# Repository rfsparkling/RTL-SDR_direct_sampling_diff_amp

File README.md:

This is a breakout board for stock RTL-SDR dongle, allowing the until known best direct sampling method for HF reception using a differential amplifer as BALUN. Right now filtering DC...14 MHz band but possible to work on 14...28 MHz band too after adding a Band Pass Filter BPF.

My design utilizes an LNA too, which adds about 20 dB of gain on HF band. Also a PI attenuator added right after to avoid saturation in the diff amp. The LNA main reason is to create good noise figure for the RX chain.

Thanks to Martin - G8JNJ for publishing his idea about a possible diff amp solution for direct sampling! Also for taking his time and working with me on that also testing and reviewing the first prototype.
http://www.g8jnj.net/softwaredefinedradio.htm

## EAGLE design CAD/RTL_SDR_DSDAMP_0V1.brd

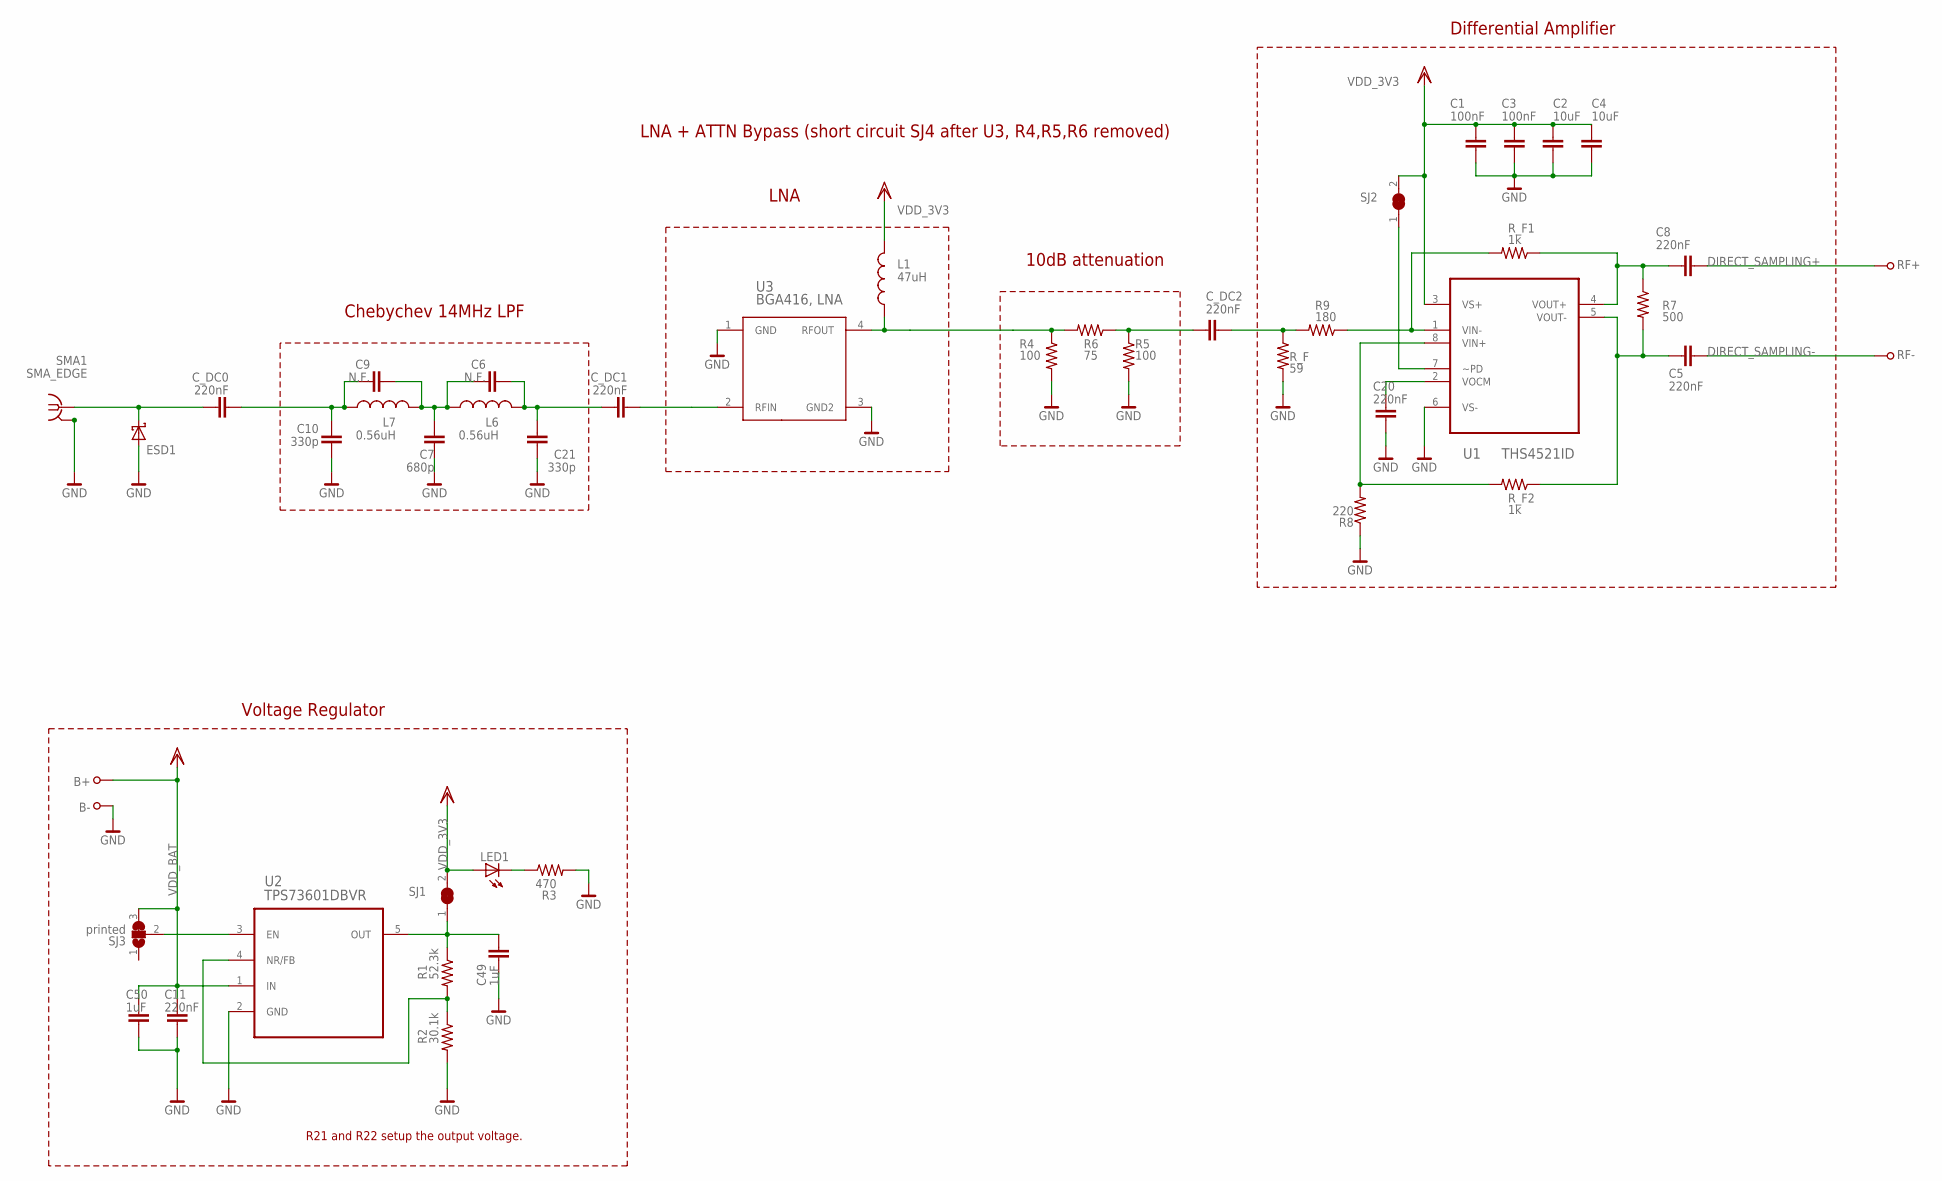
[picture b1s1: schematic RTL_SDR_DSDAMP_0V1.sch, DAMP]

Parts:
B+: TESTPOINT39MIL; TESTPOINT1,0
B-: TESTPOINT39MIL; TESTPOINT1,0
C1, C2: 100nF; 0603
C3, C4: 10uF; 0603
C5, C8, C11, C20: 220nF; 0603
C6, C9: N.F.; 0603
C7: 680p; 0603
C10, C21: 330p; 0603
C49, C50: 1uF; 0603
C_DC0, C_DC1, C_DC2: 220nF; 0603
ESD1: PGB1010603NRHF; 0603@1
L1: 47uH; L1210
L6, L7: 0.56uH; L1210
LED1: LED0603; LED-0603
R1: 52.3k; R0603
R2: 30.1k; R0603
R3: 470; R0402
R4, R5: 100; R0603
R6: 75; R0603
R7: 500; R0603
R8: 220; R0603
R9: 180; R0603
RF+: TESTPOINT39MIL; TESTPOINT1,0
RF-: TESTPOINT39MIL; TESTPOINT1,0
R_F: 59; R0603
R_F1, R_F2: 1k; R0603
SJ1, SJ2: printed; JUMPER_SMD_SJ_1
SJ3: printed; JUMPER_SMD_SJ2A
SMA1: SMA_EDGE; 142-0701-801
U1: THS4521ID; SOIC127P600X175-8N
U2: TPS73601DBVR; SOT95P280X145-5N
U3: BGA416, LNA; SOT143

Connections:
DIRECT_SAMPLING+: C8.1, RF+.1
DIRECT_SAMPLING-: C5.1, RF-.1
GND: B-.1, C1.1, C2.1, C3.1, C4.1, C7.1, C10.1, C11.1, C20.1, C21.1, C49.1, C50.1, ESD1.1 (A), R2.2, R3.2, R4.2, R5.2, R8.1, R_F.2, SMA1.RING@1 (2), SMA1.RING@2 (3), SMA1.RING@3 (4), SMA1.RING@4 (5), U1.6 (VS-), U2.2 (GND), U3.1 (GND), U3.3 (GND2)
unnamed: LED1.C, R3.1
unnamed: L1.2, R4.1, R6.2, U3.4 (RFOUT)
unnamed: C6.2, C21.2, C_DC1.1, L6.1
unnamed: C9.1, C10.2, C_DC0.2, L7.2
unnamed: C49.2, R1.1, SJ1.1, U2.5 (OUT)
unnamed: C5.2, R7.2, R_F2.1, U1.5 (VOUT-)
unnamed: C8.2, R7.1, R_F1.1, U1.4 (VOUT+)
unnamed: C_DC1.2, U3.2 (RFIN)
unnamed: C6.1, C7.2, C9.2, L6.2, L7.1
unnamed: C20.2, U1.2 (VOCM)
unnamed: R1.2, R2.1, U2.4 (NR/FB)
unnamed: SJ2.1, U1.7 (~PD)
unnamed: R8.2, R_F2.2, U1.8 (VIN+)
unnamed: SJ3.2, U2.3 (EN)
unnamed: C_DC2.1, R5.1, R6.1
unnamed: R9.1, R_F1.2, U1.1 (VIN-)
unnamed: C_DC0.1, ESD1.2 (C), SMA1.TIP (1)
unnamed: C_DC2.2, R9.2, R_F.1
VDD_3V3: C1.2, C2.2, C3.2, C4.2, L1.1, LED1.A, SJ1.2, SJ2.2, U1.3 (VS+)
VDD_BAT: B+.1, C11.2, C50.2, SJ3.3, U2.1 (IN)

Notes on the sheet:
R21 and R22 setup the output voltage.
10dB attenuation
Differential Amplifier
LNA
LNA + ATTN Bypass (short circuit SJ4 after U3, R4,R5,R6 removed)
Chebychev 14MHz LPF
Voltage Regulator

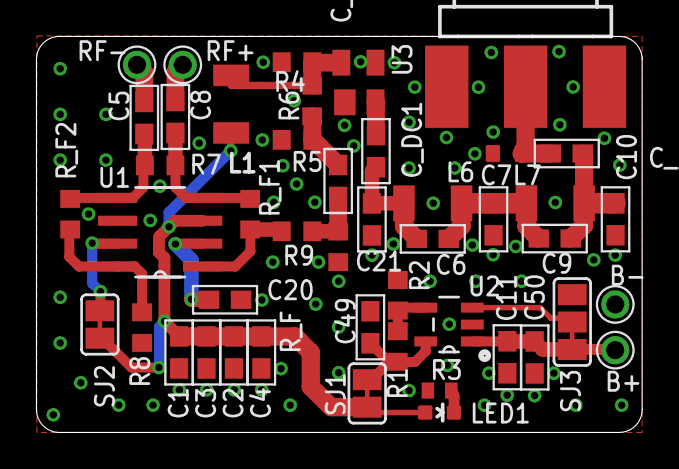
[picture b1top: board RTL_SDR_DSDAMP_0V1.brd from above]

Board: 2 copper layers, 33.7 x 22.0 mm, 46 parts (0 on the bottom side), 23 nets.

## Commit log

2016-06-14 :neckbeard: Added .gitattributes & .gitignore files
2016-06-14 adding CAD / CAM files
2016-06-14 adding pictures of prototypes
2016-06-14 Adding datasheets
2016-06-14 correcting picture
2016-06-14 Adding the missing LNA VDD bias network, updating CAD / CAM / PDF files
